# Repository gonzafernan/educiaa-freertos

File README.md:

# RTOS en placa de desarrollo EDU-CIAA para el control de un accionamiento electromecánico básico

El objetivo del trabajo es la implementación de una aplicación basada en el sistema operativo de tiempo real FreeRTOS, sobre la placa de desarrollo EDU-CIAA, para el control de un sistema electromecánico básico que tiene como fin únicamente la demostración visual de lo que sucede en la electrónica. Se busca implementar todos los conceptos fundamentales de FreeRTOS, basándose en el libro *Mastering the FreeRTOS Real Time Kernel*, por más que algunos de estos conceptos tengan una aplicación forzada y se alejen de lo práctico o lo más conveniente. Esto es porque la principal finalidad del proyecto es aprender a utilizar FreeRTOS por sobre obtener un controlador del sistema con buen criterio de diseño y eficiente.

Además, el proyecto también busca una introducción al flujo de trabajo del proyecto CIAA (Computadora Industrial Abierta Argentina). Salvo algunas excepciones, no se profundizó en la programación de los microcontroladores a nivel de registros, sino que se utilizó la capa de abstracción proveída por la librería sAPI, incluida en el firmware de dicho proyecto CIAA.

## Software y hardware utilizado
El proyecto se basa en el firmware del proyecto CIAA en su versión 3, se puede obtener más información en su [repositorio en Github](https://github.com/epernia/firmware_v3). El código fuente del firmware con todos sus ejemplos se encuentra como carpeta en este proyecto.

El trabajo consiste en el movimiento controlado del robot EEZYBOTARM MK3 publicado por EEZY robots y diseñado por Carlo Franciscone. 

Por lo tanto, además de la EDU-CIAA el hardware necesario son:

- 3 motores paso a paso monopolares 28BYJ-48 con drivers ULN2003.
- Un servomotor Tower Pro SG90 (extremo operativo del robot).
- Un display LCD 16x02 (no se utilizó comunicación I2C, sino conexión directa mediante interfaz de 4 bits).
- Un encoder rotativo incremental con pulsador como interfaz de entrada del usuario.

## ¿Cómo utilizar?
Para compilar el código solo es necesario ejecutar el comando `make` dentro de la carpeta del repositorio. Para subir a la placa EDU-CIAA el proyecto, ejecutar el comando `make download`. Si esto último da error remitirse a la documentación del firmware o contactarme para solucionarlo (el problema puede llegar a ser de permisos del sistema).

La conexión del hardware debe se describe en la siguiente imagen de forma simplificada (Como trabajo a futuro es necesario clarificar esta imagen e incorporar las PCB diseñadas):

## Estructura del proyecto
En la siguiente imagen se  puede observar de forma simplificada la estructura que presenta el código del proyecto, los diferentes módulos y la forma en que se comunican entre sí.

Para información más detallada, ir al [informe](docs/informe/main.pdf) presentado del trabajo.

## Contribuir
El proyecto ya fue presentado, sin embargo, como todos mis proyectos sigue abierto a recomendaciones, críticas o cambios que parezcan oportunos a cualquier interesado. Para proponer alguna modificación sencillamente deben contactarme a mi mail o redes sociales, o directamente hacer un *pull-request* con los cambios que se desean realizar. Será un placer intercambiar opiniones y agregar al proyecto cualquier mejora por mínima que sea.

### Estilo de código
La escritura del código en C sigue los lineamientos de FreeRTOS que se encuentran en el libro *Mastering the freeRTOS Real Time Kernel*, para el nombre de funciones, variables, definiciones, etc. En cuánto a los comentarios y toda la documentación externa al código en sí, se siguió el proyecto Doxygen.

## Créditos
Es importante agradecer a Eric Pernia, uno de los desarrolladores del firmware de la placa EDU-CIAA que solucionó dudas mientras me iniciaba con la placa de desarrollo. El proyecto fue desarrollado para la cátedra Microcontroladores y Electrónica de Potencia de la Facultad de Ingeniería de la Universidad Nacional de Cuyo. El profesor Ing. Eduardo Iriarte salvó muchísimas dudas tanto de electrónica, específicas de la placa EDU-CIAA y conceptuales de RTOS y programación de sistemas embebidos en C.

## Licencia 
MIT © Gonzalo G. Fernández

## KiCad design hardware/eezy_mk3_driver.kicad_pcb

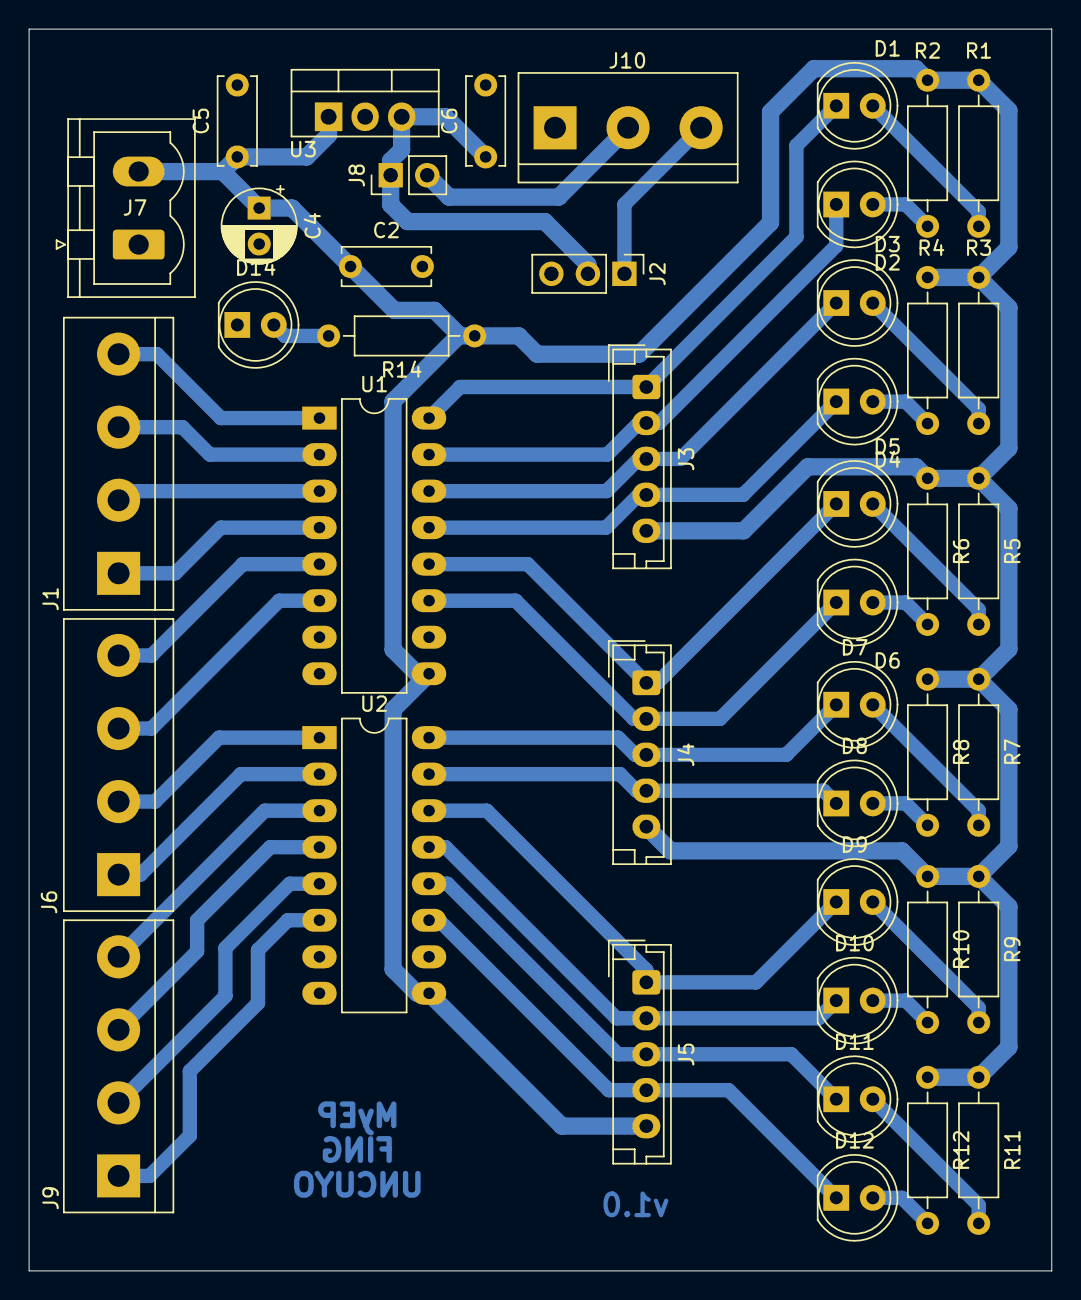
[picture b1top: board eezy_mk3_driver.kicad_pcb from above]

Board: 2 copper layers, 71.1 x 86.4 mm, 43 parts (0 on the bottom side), 42 nets.

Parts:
C2, C6: 0.1uF; C_Disc_D6.0mm_W2.5mm_P5.00mm
C4: 10uF; CP_Radial_D5.0mm_P2.50mm
C5: 0.33uF; C_Disc_D6.0mm_W2.5mm_P5.00mm
D1, D2, D3, D4, D5, D6, D7, D8, D9, D10, D11, D12, D14: LED; LED_D5.0mm
J1: IN_STP1; TerminalBlock_bornier-4_P5.08mm
J2: OUT_SERVO; PinHeader_1x03_P2.54mm_Vertical
J3: OUT_STP1; JST_EH_B5B-EH-A_1x05_P2.50mm_Vertical
J4: OUT_STP2; JST_EH_B5B-EH-A_1x05_P2.50mm_Vertical
J5: OUT_STP3; JST_EH_B5B-EH-A_1x05_P2.50mm_Vertical
J6: IN_STP2; TerminalBlock_bornier-4_P5.08mm
J7: POWER_12V; PhoenixContact_MSTBVA_2,5_2-G-5,08_1x02_P5.08mm_Vertical
J8: POWER_JUMPER_5V; PinHeader_1x02_P2.54mm_Vertical
J9: IN_STP3; TerminalBlock_bornier-4_P5.08mm
J10: IN_SERVO; TerminalBlock_bornier-3_P5.08mm
R1, R2, R3, R4, R5, R6, R7, R8, R9, R10, R11, R12, R14: 1k; R_Axial_DIN0207_L6.3mm_D2.5mm_P10.16mm_Horizontal
U1, U2: ULN2003; DIP-16_W7.62mm_LongPads
U3: LM7805_TO220; TO-220-3_Vertical

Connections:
5V_uC: J8.2, J10.2
+5V: C6.1, J2.2, J8.1, U3.3
+12V: C2.1, C4.1, C5.1, J3.5, J4.5, J5.5, J7.2, R1.1, R2.1, R3.1, R4.1, R5.1, R6.1, R7.1, R8.1, R9.1, R10.1, R11.1, R12.1, R14.1, U1.9, U2.9, U3.1
GND: C2.2, C4.2, C5.2, C6.2, D14.1, J2.3, J7.1, J10.1, U1.8, U2.8, U3.2
unnamed: D1.1, J3.1, U1.16
unnamed: D1.2, R1.2
unnamed: D2.1, J3.2, U1.15
unnamed: D2.2, R2.2
unnamed: D3.1, J3.3, U1.14
unnamed: D3.2, R3.2
unnamed: D4.1, J3.4, U1.13
unnamed: D4.2, R4.2
unnamed: D5.1, J4.1, U1.12
unnamed: D5.2, R5.2
unnamed: D6.1, J4.2, U1.11
unnamed: D6.2, R6.2
unnamed: D7.1, J4.3, U2.16
unnamed: D7.2, R7.2
unnamed: D8.1, J4.4, U2.15
unnamed: D8.2, R8.2
unnamed: D9.1, J5.1, U2.14
unnamed: D9.2, R9.2
unnamed: D10.1, J5.2, U2.13
unnamed: D10.2, R10.2
unnamed: D11.1, J5.3, U2.12
unnamed: D11.2, R11.2
unnamed: D12.1, J5.4, U2.11
unnamed: D12.2, R12.2
unnamed: D14.2, R14.2
unnamed: J1.1, U1.4
unnamed: J1.2, U1.3
unnamed: J1.3, U1.2
unnamed: J1.4, U1.1
unnamed: J6.1, U2.2
unnamed: J6.2, U2.1
unnamed: J6.3, U1.6
unnamed: J6.4, U1.5
unnamed: J9.1, U2.6
unnamed: J9.2, U2.5
unnamed: J9.3, U2.4
unnamed: J9.4, U2.3
SERVO_PWM: J2.1, J10.3

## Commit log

2020-01-04 added firmware_v3 module
2020-01-04 added README and first config
2020-01-04 added link to scripts folder to make download
2020-01-13 added docs folder and first example
2020-01-13 added modulos edu ciaa imagen
2020-01-13 Create LICENSE
2020-01-14 added first example freeRTOS
2020-01-14 rm out example freeRTOS
2020-01-14 update ejemplo 1
2020-01-14 added get-port bash script
2020-01-14 example 1 variation
2020-01-15 added 2nd example freeRTOS
2020-01-15 update examples
2020-01-15 added 3rd example
2020-01-17 updated gitignore
2020-01-21 added encoder example, first try
2020-01-23 added task states image
2020-01-23 updated task states image
2020-01-23 added 4th example freeRTOS
2020-01-24 updated firmware
2020-01-24 added ponchos submodule
2020-01-31 added first app sketch with lcd message
2020-02-06 working encoder with deferred interrupt processing
2020-02-09 added sct pwm related images
2020-02-09 funciones asociadas al control del servo
2020-02-14 added working uart communication
2020-06-29 [update] general local update resuming project
2020-06-29 [deleted] clean for dev
2020-06-29 [new] firmware v3 1.3.0
2020-06-29 [update] symbolic link to firmware resources
2020-06-30 [new] uart with rtos queues
2020-07-02 [update] uart without debug led
2020-07-02 [new] app folder with uart implementation
2020-07-06 [new] simple stepper example
2020-07-08 [fix] ticks to wait to portMAX_DELAY
2020-07-08 [update] simple stepper example
2020-07-09 [update] stepper control
2020-07-10 [update] stepper con consigna por uart secuencial + prioridades de tarea
2020-07-10 [update] error handling for stepper setpoints
2020-07-11 [fix] eliminar valor absoluta en estructura de stepper
2020-07-11 [new] encoder files
2020-07-11 [update] program.mk
2020-07-11 [new] led blink task
2020-07-11 [new] driver uln2003 files and multiple stepper working
2020-07-11 [new] encoder working
2020-07-12 [update] enconder enviando consignas correctamente
2020-07-12 [update] encoder motor selection
2020-07-13 [update] uart doxygen doc + configMAX_SYSCALL_INTERRUPT_PRIORITY
2020-07-13 [update] cola de consignas con mutex
2020-07-13 [update] actualización de diagramas
2020-07-13 [delete] limpiar master para merge con dev
2020-07-13 [new] informe en LaTeX
2020-07-19 [new] servo funcionando, ver problemas ¿de memoria?
2020-07-19 [update] servo+encoder+stepper+uart funcionando
2020-07-19 [update] event group en stepper funcionando (falta consigna a varios motores)
2020-08-06 [update] consigna multiple stepper
2020-08-27 [update] tercer motor con error en conexión
2020-08-27 [new] pcb driver eezy mk3
2020-09-10 [update] actualización general con display y fix encoder
2020-09-10 [update] encoder actualiza seleccion en display
2020-09-12 [new] circular buffer not working
2020-09-12 [update] deferring work to the RTOS daemon task funcionando
2020-09-12 [update] logica de display funcionando
2020-09-12 [update] pwm de servo funcionando
2020-09-14 [update] encoder funcionando, cambio en prioridades
2020-09-14 [update] enconder conconsignas a servo
2020-09-15 [fix] bugs en display
2020-09-16 [update] informe presentado, actualización de display
2020-09-16 [fix] bug en ángulo pendiente solucionado
2020-09-16 [update/fix] display funcionando sin i2c, fix bug en servo
2020-09-16 [update] documentacion del código
2020-09-16 [fix] bug en consigna a motores pap
2020-09-16 [update] documentación del proyecto
2020-09-25 [new] presentacion de examen final
